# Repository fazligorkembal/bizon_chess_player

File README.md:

# ♟️ Bizon Chess Player

Bizon Chess Player is a ROS2-based autonomous dual-arm chess system running in simulation.  
Two robotic manipulators (`bizon2` and `bizon3`) play chess against each other in NVIDIA Isaac Sim — one controls the white pieces, the other controls the black pieces.

The project integrates perception, AI decision-making, motion planning, and behavior orchestration into a fully containerized robotics pipeline.

---

## 🏗 System Overview

- **Simulation**: NVIDIA Isaac Sim v5.1.0 renders the physics environment and camera stream.
- **Robot Control**: MoveIt2 performs motion planning for each robotic arm.
- **Perception**: Custom-trained Ultralytics YOLO26 model, converted layer-by-layer into a TensorRT engine and optimized for this system, detects chess pieces and reconstructs the board state.
- **Chess Engine**: Stockfish computes the optimal move for each side.
- **Decision & Execution**: Behavior Trees (BehaviorTree.CPP) orchestrate the full move execution pipeline (straight move, capture, promotion, en passant, promotion capture)
- **Containerization**: Entire stack runs inside Docker containers built on NVIDIA NGC images.

---

## Architecture

```
Isaac Sim (physics + camera) ──► YOLO perception ──►  Board State
                                                           │
                                                    Stockfish (AI move)
                                                           │
                                              Behavior Tree (orchestration)
                                                           │
                                                MoveIt2 (motion planning)
                                                           │
                                              Robot Arm (pick & place piece)
```

---

## ⚙️ Requirements

- Ubuntu 22.04
- NVIDIA Isaac Sim 5.1.0
- Docker & Docker Compose
- NVIDIA NGC login (for container access)

> It is recommended to clone the repository under:
> `/home/<username>/Documents/projects/`

If another location is used, update the project path hardcoded inside `isaac_sim_standalone.sh`.

## Pre Install
- Install NVIDIA Isaac Sim 5.1.0 with ROS 2 container compatibility.
- Download the asset and model folders, then extract them into the project root directory
- Install Nvidia Docker Containers and login NGC
- Install docker-compose
- Download https://drive.google.com/file/d/1CkLfItfGiQZPKxY0u-t-2HWdBcdwbd3Y/view?usp=sharing and unzip. And move assets and models folder to project root directory.

---

## 🐳 Docker Initialization

Run the project inside the Docker container:

```bash
# Open a new docker terminal
sudo docker-compose -f docker/docker-compose-x86.yml run bizon_chess_player bash

# Install BehaviorTree.Cpp
cd ros_env/src
git clone https://github.com/BehaviorTree/BehaviorTree.CPP.git

# Build the workspace (the colcon workspace is ros_env/, not the project root)
cd <project_root>/ros_env
colcon build
source install/setup.bash

# Install Stockfish
cd <project_root>
git clone https://github.com/official-stockfish/Stockfish.git
cd Stockfish/src
make -j profile-build
```

## 🎮 Start Simulation

Open a new terminal:
```
./isaac_sim_standalone.sh
```

## 🤖 Multi-Robot Control

One terminal per robot (two total for dual-arm operation).

Enter the container, and source the workspace in every terminal:
```
sudo docker container exec -it <container_id> bash
source ros_env/install/setup.bash
```
🔹 Robot: bizon2 (White)
```
ros2 launch bizon_player_bringup bizon_player.launch.py prefix:=bizon2
```
🔹 Robot: bizon3 (Black)
```
ros2 launch bizon_player_bringup bizon_player.launch.py prefix:=bizon3
```

`bizon_player.launch.py` starts MoveIt and ros2_control, then `behavior_server` and the
lifecycle manager, then the behavior tree client, waiting between each stage. It selects the
behavior parameter file that matches `prefix`. On a slower machine, raise the waits:

```
ros2 launch bizon_player_bringup bizon_player.launch.py prefix:=bizon2 lifecycle_delay:=20.0 client_delay:=30.0
```

Both delays are measured from launch start, so `client_delay` must stay above
`lifecycle_delay`. Run `ros2 launch bizon_player_bringup bizon_player.launch.py --show-args`
for the full argument list.

### Running the stages separately

To debug one layer in isolation, the three underlying launch files still work on their own —
three terminals per robot, started in this order:

```
ros2 launch bizon_player_bringup bizon_player_bringup.launch.py prefix:=bizon2
ros2 launch bizon_player_bringup bizon_lifecycle_dev.launch.py namespace:=bizon2
ros2 run bizon_behavior_clients bizon_behavior_tree_client_main --ros-args -r __ns:=/bizon2 -p use_sim_time:=true
```

# ⚠️ Notes
* This project is currently in alpha stage.

* Startup order is important.

* Namespaces are currently partially hardcoded (bizon2, bizon3).

* The system currently supports simultaneous control of two robots.

* Task-specific logic and robot-specific hardcoded parameters limit generalization to other robots or tasks.

* Full namespace abstraction and improved generalization are planned for future projects. 

# 📚 References

- [Ultralytics](https://github.com/ultralytics/ultralytics) – YOLO implementation framework  
- [BehaviorTree.CPP](https://github.com/BehaviorTree/BehaviorTree.CPP) – Behavior tree library for robotics  
- [Nav2](https://github.com/ros-navigation/navigation2) – ROS 2 Navigation framework  
- [Stockfish](https://github.com/official-stockfish/Stockfish) – Chess engine  
- [tensorrtx (YOLO26)](https://github.com/wang-xinyu/tensorrtx/tree/master/yolo26) – TensorRT implementation

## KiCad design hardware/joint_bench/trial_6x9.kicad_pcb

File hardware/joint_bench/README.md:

# Joint0 bench hardware

Everything here except `nets.yaml`, the `trial_*.yaml` placement files and this README is
generated. Edit the YAML, then regenerate:

    python3 tools/kicad_gen/generate.py

That writes the schematic, runs KiCad's ERC, checks the exported netlist against
`nets.yaml`, and rebuilds each placement board with its drawings and soldering checklist.
KiCad does not need to be installed: `scripts/kicad-cli` runs `kicad-cli` from the
`kicad/kicad:10.0.6-full` Docker image, pinned by digest. Opening the files in a local
KiCad 8 or later works too, for viewing.

| File | What it is |
|---|---|
| `nets.yaml` | Source of truth: parts and nets. |
| `trial_6x9.yaml` | Where each part sits on the 6 x 9 cm trial board, in holes. |
| `joint_bench.kicad_sch` | Schematic. Every pin ends in a net label; read it by label. |
| `exports/joint_bench.pdf` | The schematic, for printing. |
| `trial_6x9.kicad_pcb` | Placement board. Not for fabrication. |
| `exports/trial_6x9_top.pdf` | Component side, 1:1. Print at 100 % ("actual size"). |
| `exports/trial_6x9_bottom_mirrored.pdf` | Solder side, mirrored, 1:1: wire from this one. |
| `trial_6x9_checklist.md` | Every wire to solder, then continuity and short checks. |

Design: `docs/superpowers/specs/2026-10-16-joint0-bench-design.md`. Bench procedure:
`docs/hardware/joint-bench-stage-a-runbook.md`.

Stage-B software preparation and remaining hardware-facing work:
`docs/hardware/joint-bench-stage-b-preparation.md`.

## Capacitors ordered — 2026-11-08

The user confirmed ordering the following exact products from Özdisan. This records the
order, not receipt or inspection of the parts; purchased quantities were not confirmed.
All three products are through-hole, not SMD.

| Use | Ordered part | Supplier link |
|---|---|---|
| Across each TMC2209's VM/GND, close to the driver | Koshin `PKLH-050V101MG120-T/A5.0`, 100 µF / 50 V, low impedance, 105 °C, 10 × 12 mm body, 5 mm lead spacing | [Özdisan](https://www.ozdisan.com/p/aluminyum-kapasitorler-180/koshin-pklh-050v101mg120-t-a5-0-355181) |
| Motor power input bulk capacitor | Koshin `PKLH-063V102MJ355`, 1000 µF / **63 V**, low impedance, 105 °C, 16 × 35.5 mm body, 7.5 mm lead spacing | [Özdisan](https://www.ozdisan.com/p/aluminyum-kapasitorler-180/koshin-pklh-063v102mj355-345727) |
| Ceramic bypass across the driver's VM/GND, parallel to the 100 µF capacitor | Kingtronics `MKT0805B104K500PF3R`, 100 nF / 50 V, X7R, ±10%, 5.08 mm lead spacing | [Özdisan](https://www.ozdisan.com/p/multilayer-kapasitorler-182/kingtronics-mkt0805b104k500pf3r-383365) |

The **1000 µF / 63 V** part deliberately replaces the **1000 µF / 50 V** originally specified
for the planned 12–24 V motor supply. Capacitance is unchanged; 63 V is the capacitor's
voltage rating, not the supply setting or a voltage clamp. The TMC2209's supply limits remain
unchanged, and this substitution requires no firmware change. Allow for the ordered part's
larger body and 7.5 mm lead spacing when laying out stage B. Both electrolytics are polarized:
connect positive to VM and negative to GND.

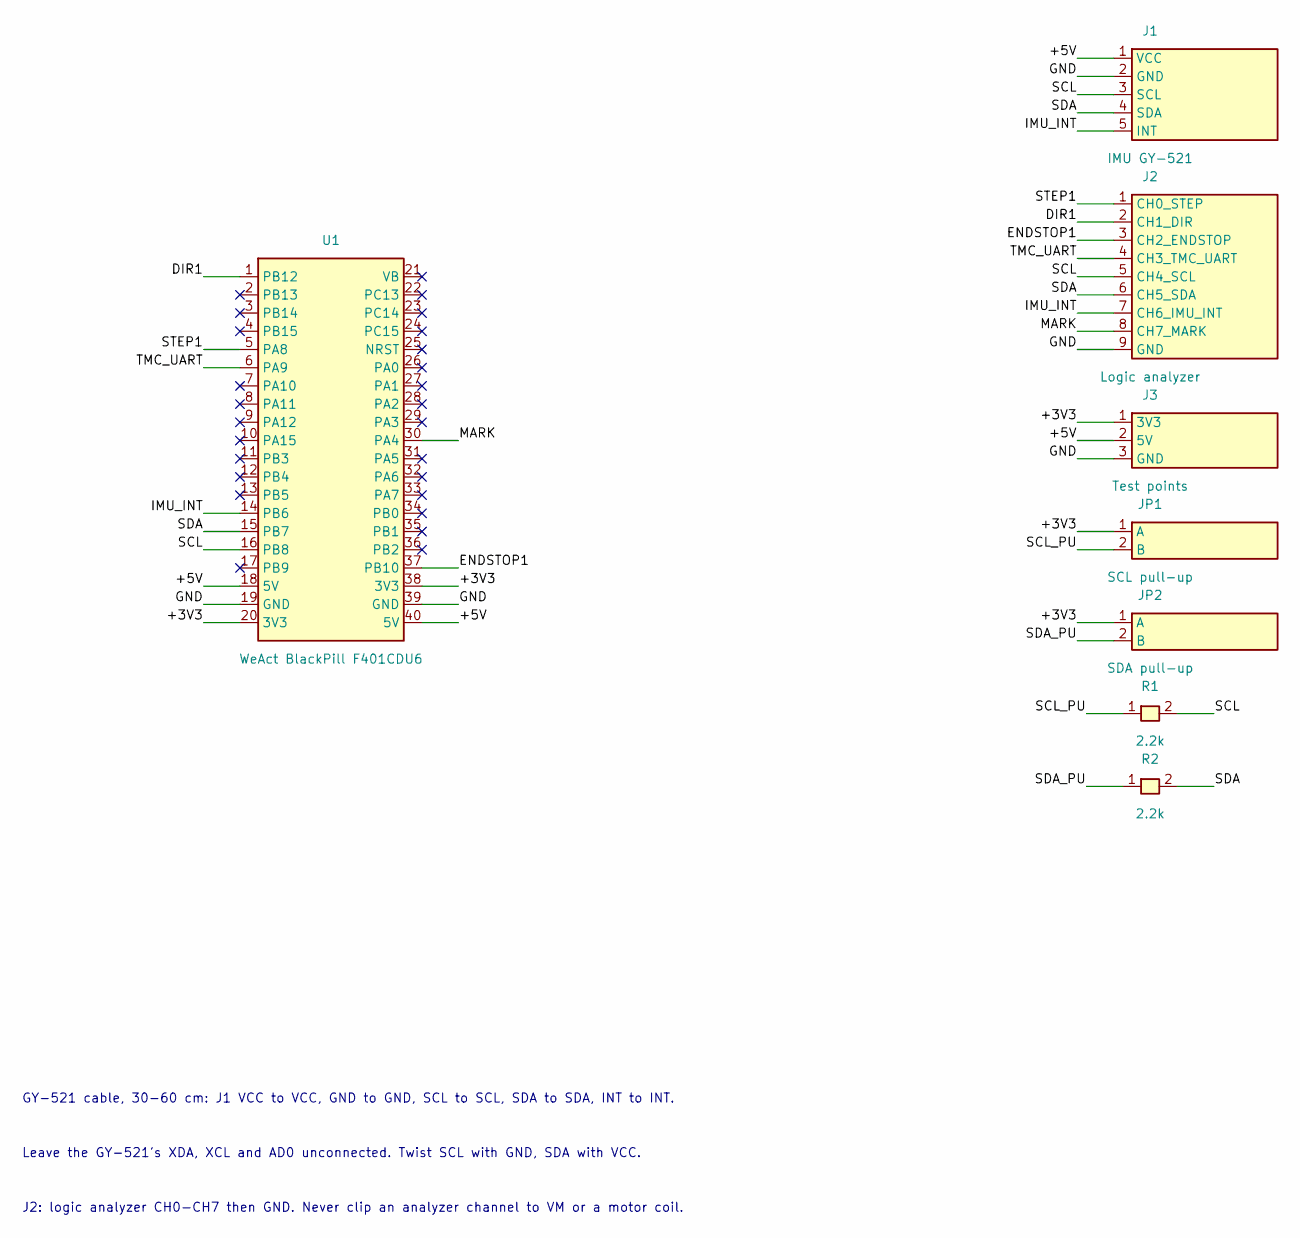
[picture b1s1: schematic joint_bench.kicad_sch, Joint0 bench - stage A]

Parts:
J1: IMU GY-521
J2: Logic analyzer
J3: Test points
JP1: SCL pull-up
JP2: SDA pull-up
R1, R2: 2.2k
U1: WeAct BlackPill F401CDU6

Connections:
+3V3: J3.1 (3V3), JP1.1 (A), JP2.1 (A), U1.20 (3V3), U1.38 (3V3)
+5V: J1.1 (VCC), J3.2 (5V), U1.18 (5V), U1.40 (5V)
DIR1: J2.2 (CH1_DIR), U1.1 (PB12)
ENDSTOP1: J2.3 (CH2_ENDSTOP), U1.37 (PB10)
GND: J1.2 (GND), J2.9 (GND), J3.3 (GND), U1.19 (GND), U1.39 (GND)
IMU_INT: J1.5 (INT), J2.7 (CH6_IMU_INT), U1.14 (PB6)
MARK: J2.8 (CH7_MARK), U1.30 (PA4)
SCL: J1.3 (SCL), J2.5 (CH4_SCL), R1.2, U1.16 (PB8)
SCL_PU: JP1.2 (B), R1.1
SDA: J1.4 (SDA), J2.6 (CH5_SDA), R2.2, U1.15 (PB7)
SDA_PU: JP2.2 (B), R2.1
STEP1: J2.1 (CH0_STEP), U1.5 (PA8)
TMC_UART: J2.4 (CH3_TMC_UART), U1.6 (PA9)

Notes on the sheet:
GY-521 cable, 30-60 cm: J1 VCC to VCC, GND to GND, SCL to SCL, SDA to SDA, INT to INT.
Leave the GY-521's XDA, XCL and AD0 unconnected. Twist SCL with GND, SDA with VCC.
J2: logic analyzer CH0-CH7 then GND. Never clip an analyzer channel to VM or a motor coil.

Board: 2 copper layers, 8 parts (0 on the bottom side), 13 nets, no tracks yet.

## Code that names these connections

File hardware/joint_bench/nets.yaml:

# Joint0 bench, stage A: BlackPill, IMU connector, logic-analyzer header.
#
# This file is the source of truth for the board. The schematic, the placement board and
# the soldering checklist are generated from it by tools/kicad_gen; never edit those by
# hand. Pin references are REF.NAME (a module pin name such as GND covers every pin with
# that name) or REF.NUMBER. Design: docs/superpowers/specs/2026-10-16-joint0-bench-design.md
title: Joint0 bench - stage A

parts:
  U1: {kind: blackpill, value: WeAct BlackPill F401CDU6}
  # The GY-521 sits on the platform beside the chessboard, 30-60 cm away; this is the
  # perfboard end of its cable. The module breaks out no FSYNC pin.
  J1: {kind: header, value: IMU GY-521, pins: [VCC, GND, SCL, SDA, INT]}
  J2:
    kind: header
    value: Logic analyzer
    pins: [CH0_STEP, CH1_DIR, CH2_ENDSTOP, CH3_TMC_UART, CH4_SCL, CH5_SDA, CH6_IMU_INT, CH7_MARK, GND]
  J3: {kind: header, value: Test points, pins: [3V3, 5V, GND]}
  # 2.2k pull-ups in parallel with the GY-521's own. Open the jumpers when the module's
  # pull-ups alone already measure 2.7k or less, or the bus sinks more than 3 mA.
  JP1: {kind: header, value: SCL pull-up, pins: [A, B]}
  JP2: {kind: header, value: SDA pull-up, pins: [A, B]}
  R1: {kind: resistor, value: 2.2k}
  R2: {kind: resistor, value: 2.2k}

nets:
  +5V: [U1.5V, J1.VCC, J3.5V]
  GND: [U1.GND, J1.GND, J2.GND, J3.GND]
  +3V3: [U1.3V3, J3.3V3, JP1.A, JP2.A]
  SCL: [U1.PB8, J1.SCL, J2.CH4_SCL, R1.2]
  SDA: [U1.PB7, J1.SDA, J2.CH5_SDA, R2.2]
  SCL_PU: [JP1.B, R1.1]
  SDA_PU: [JP2.B, R2.1]
  IMU_INT: [U1.PB6, J1.INT, J2.CH6_IMU_INT]
  MARK: [U1.PA4, J2.CH7_MARK]
  # Stage-B signals, brought to the analyzer header now so the pins can be probed from
  # the first board onward.
  STEP1: [U1.PA8, J2.CH0_STEP]
  DIR1: [U1.PB12, J2.CH1_DIR]
  ENDSTOP1: [U1.PB10, J2.CH2_ENDSTOP]
  TMC_UART: [U1.PA9, J2.CH3_TMC_UART]
